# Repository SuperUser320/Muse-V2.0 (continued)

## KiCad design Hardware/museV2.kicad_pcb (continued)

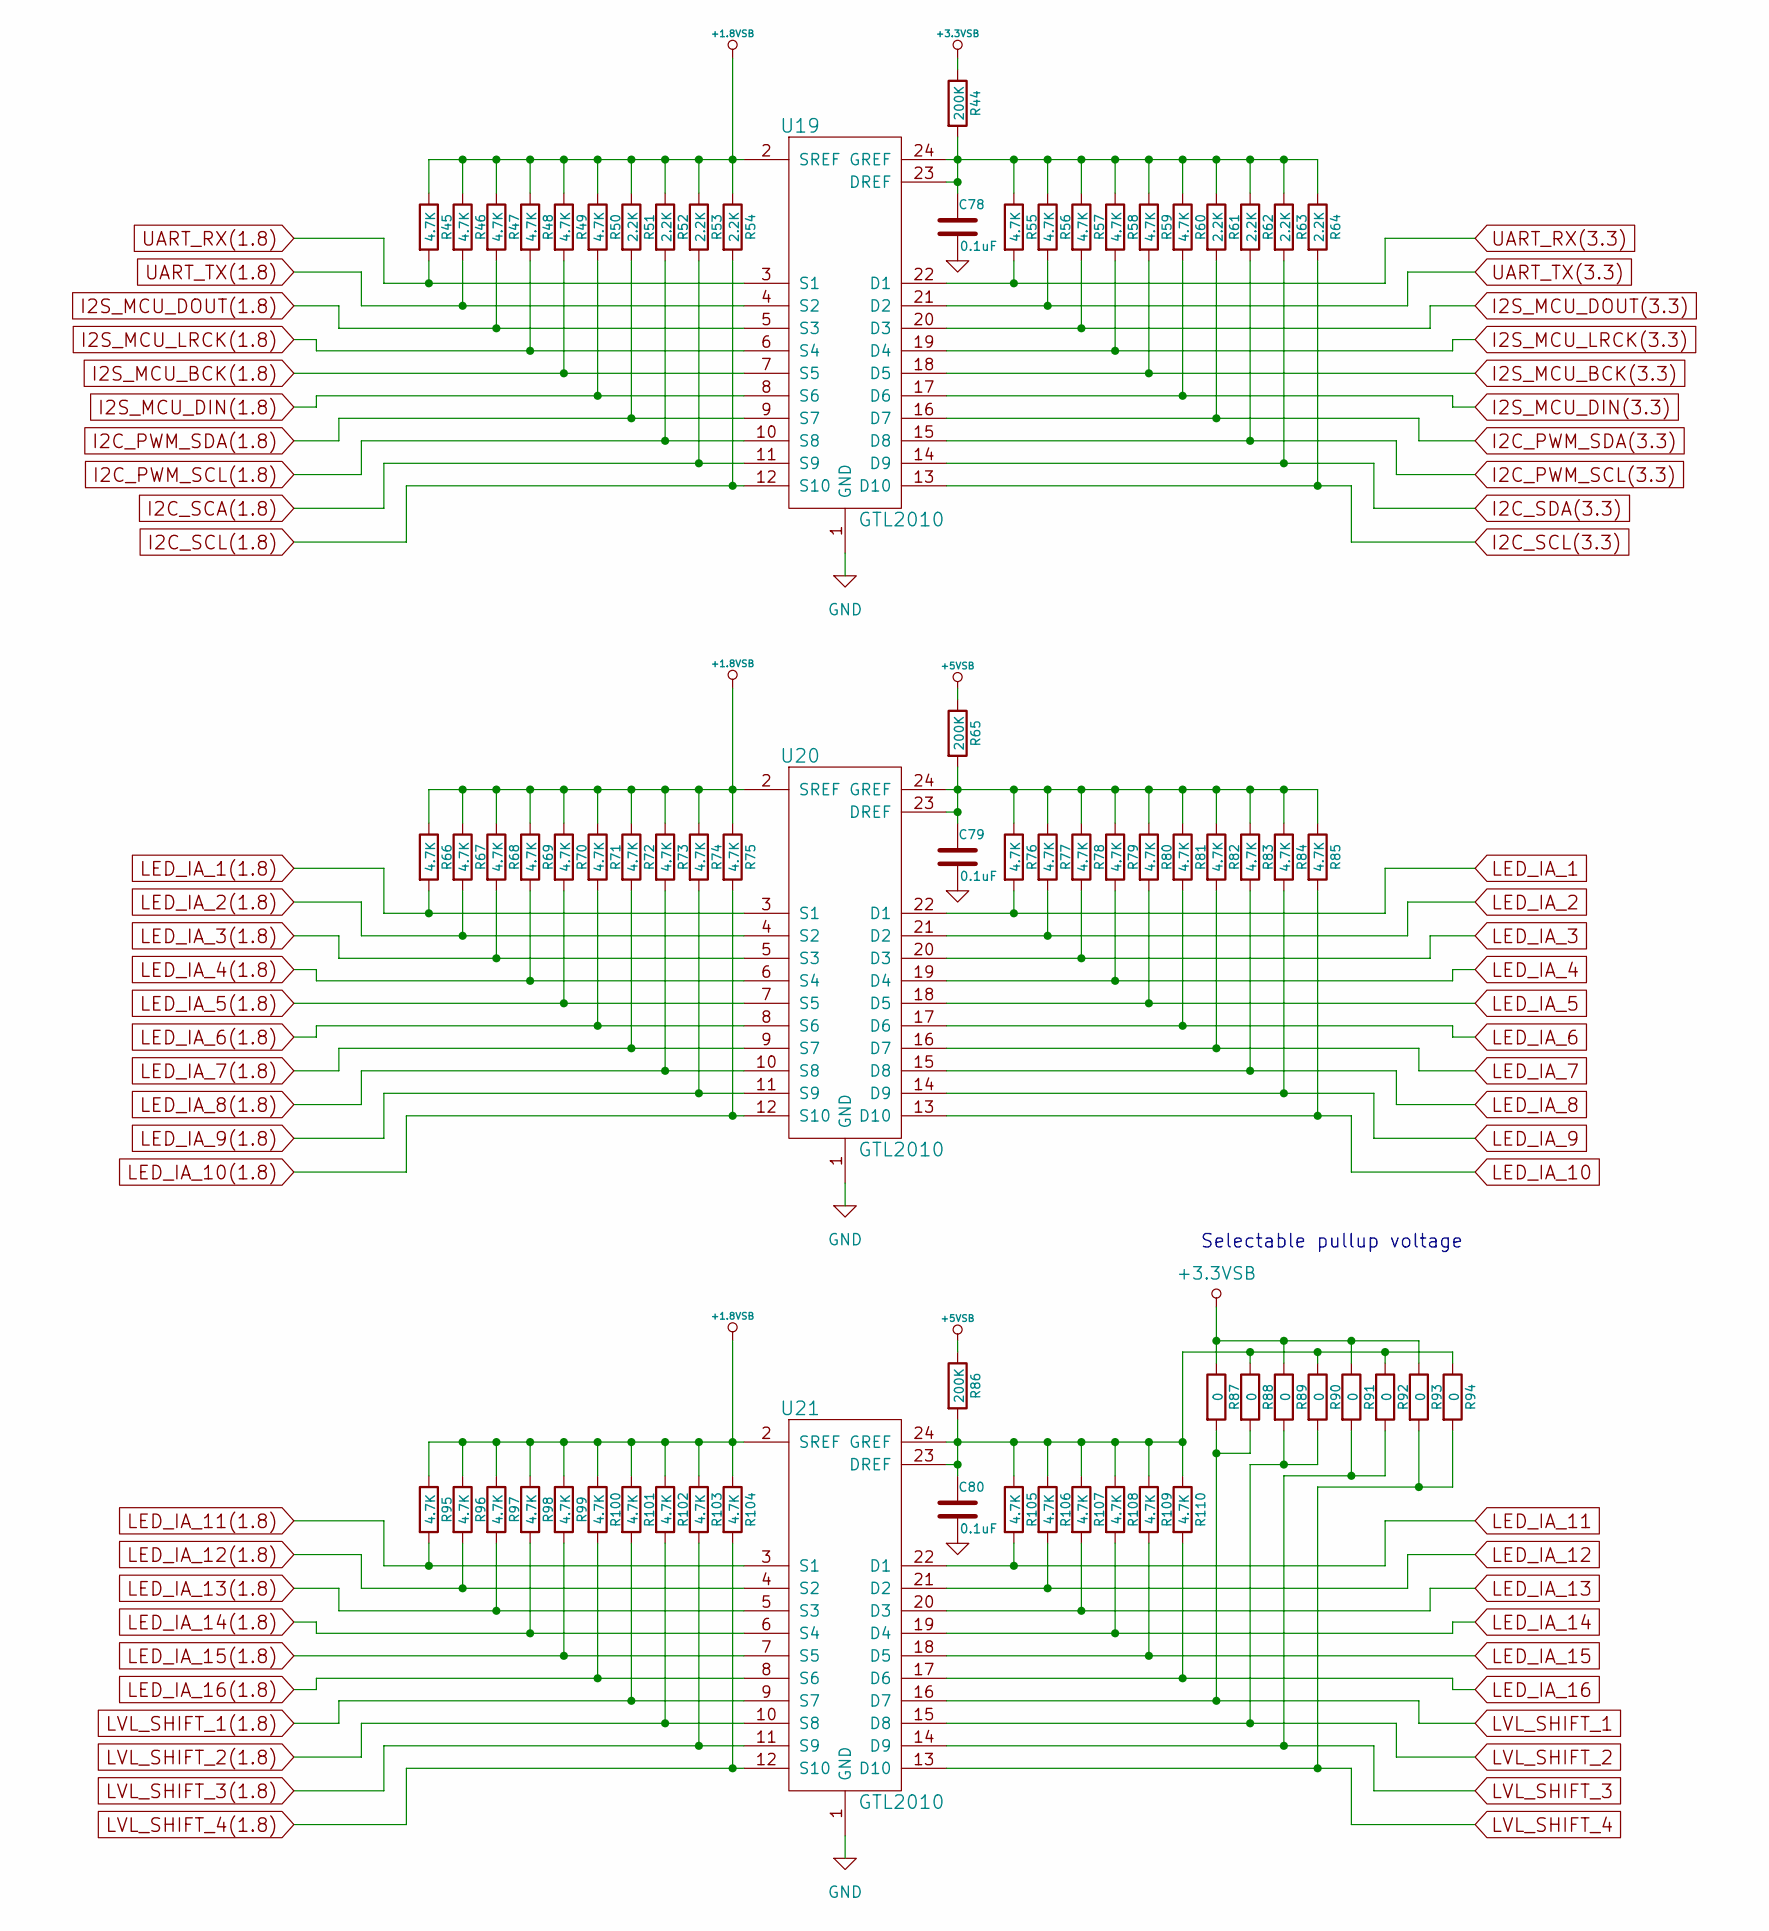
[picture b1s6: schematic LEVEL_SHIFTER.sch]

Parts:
C78, C79, C80: 0.1uF; C_0402
R44, R65, R86: 200K; R_0402
R45, R46, R47, R48, R49, R50, R55, R56, R57, R58, R59, R60, R66, R67, R68, R69, R70, R71, R72, R73, R74, R75, R76, R77, R78, R79, R80, R81, R82, R83, R84, R85, R95, R96, R97, R98, R99, R100, R101, R102, R103, R104, R105, R106, R107, R108, R109, R110: 4.7K; R_0402
R51, R52, R53, R54, R61, R62, R63, R64: 2.2K; R_0402
R87, R88, R89, R90, R91, R92, R93, R94: 0; R_0603_HandSoldering
U19, U20, U21: GTL2010; SSOP-24_5.3x8.2mm_Pitch0.65mm

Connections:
+1.8VSB: R45.1, R46.1, R47.1, R48.1, R49.1, R50.1, R51.1, R52.1, R53.1, R54.1, R66.1, R67.1, R68.1, R69.1, R70.1, R71.1, R72.1, R73.1, R74.1, R75.1, R95.1, R96.1, R97.1, R98.1, R99.1, R100.1, R101.1, R102.1, R103.1, R104.1, U19.2 (SREF), U20.2 (SREF), U21.2 (SREF); also elsewhere on the board
+3.3VSB: R44.1, R87.1, R89.1, R91.1, R93.1; also elsewhere on the board
+5VSB: R65.1, R86.1; also elsewhere on the board
GND: C78.2, C79.2, C80.2, U19.1 (GND), U20.1 (GND), U21.1 (GND); also elsewhere on the board
I2C_PWM_SCL(1.8): R52.2, U19.10 (S8); also elsewhere on the board
I2C_PWM_SCL(3.3): R62.2, U19.15 (D8); also elsewhere on the board
I2C_PWM_SDA(1.8): R51.2, U19.9 (S7); also elsewhere on the board
I2C_PWM_SDA(3.3): R61.2, U19.16 (D7); also elsewhere on the board
I2C_SCA(1.8): R53.2, U19.11 (S9); also elsewhere on the board
I2C_SCL(1.8): R54.2, U19.12 (S10); also elsewhere on the board
I2C_SCL(3.3): R64.2, U19.13 (D10); also elsewhere on the board
I2C_SDA(3.3): R63.2, U19.14 (D9); also elsewhere on the board
I2S_MCU_BCK(1.8): R49.2, U19.7 (S5); also elsewhere on the board
I2S_MCU_BCK(3.3): R59.2, U19.18 (D5); also elsewhere on the board
I2S_MCU_DIN(1.8): R50.2, U19.8 (S6); also elsewhere on the board
I2S_MCU_DIN(3.3): R60.2, U19.17 (D6); also elsewhere on the board
I2S_MCU_DOUT(1.8): R47.2, U19.5 (S3); also elsewhere on the board
I2S_MCU_DOUT(3.3): R57.2, U19.20 (D3); also elsewhere on the board
I2S_MCU_LRCK(1.8): R48.2, U19.6 (S4); also elsewhere on the board
I2S_MCU_LRCK(3.3): R58.2, U19.19 (D4); also elsewhere on the board
LED_IA_1: R76.2, U20.22 (D1); also elsewhere on the board
LED_IA_1(1.8): R66.2, U20.3 (S1); also elsewhere on the board
LED_IA_2: R77.2, U20.21 (D2); also elsewhere on the board
LED_IA_2(1.8): R67.2, U20.4 (S2); also elsewhere on the board
LED_IA_3: R78.2, U20.20 (D3); also elsewhere on the board
LED_IA_3(1.8): R68.2, U20.5 (S3); also elsewhere on the board
LED_IA_4: R79.2, U20.19 (D4); also elsewhere on the board
LED_IA_4(1.8): R69.2, U20.6 (S4); also elsewhere on the board
LED_IA_5: R80.2, U20.18 (D5); also elsewhere on the board
LED_IA_5(1.8): R70.2, U20.7 (S5); also elsewhere on the board
LED_IA_6: R81.2, U20.17 (D6); also elsewhere on the board
LED_IA_6(1.8): R71.2, U20.8 (S6); also elsewhere on the board
LED_IA_7: R82.2, U20.16 (D7); also elsewhere on the board
LED_IA_7(1.8): R72.2, U20.9 (S7); also elsewhere on the board
LED_IA_8: R83.2, U20.15 (D8); also elsewhere on the board
LED_IA_8(1.8): R73.2, U20.10 (S8); also elsewhere on the board
LED_IA_9: R84.2, U20.14 (D9); also elsewhere on the board
LED_IA_9(1.8): R74.2, U20.11 (S9); also elsewhere on the board
LED_IA_10: R85.2, U20.13 (D10); also elsewhere on the board
LED_IA_10(1.8): R75.2, U20.12 (S10); also elsewhere on the board
LED_IA_11: R105.2, U21.22 (D1); also elsewhere on the board
LED_IA_11(1.8): R95.2, U21.3 (S1); also elsewhere on the board
LED_IA_12: R106.2, U21.21 (D2); also elsewhere on the board
LED_IA_12(1.8): R96.2, U21.4 (S2); also elsewhere on the board
LED_IA_13: R107.2, U21.20 (D3); also elsewhere on the board
LED_IA_13(1.8): R97.2, U21.5 (S3); also elsewhere on the board
LED_IA_14: R108.2, U21.19 (D4); also elsewhere on the board
LED_IA_14(1.8): R98.2, U21.6 (S4); also elsewhere on the board
LED_IA_15: R109.2, U21.18 (D5); also elsewhere on the board
LED_IA_15(1.8): R99.2, U21.7 (S5); also elsewhere on the board
LED_IA_16: R110.2, U21.17 (D6); also elsewhere on the board
LED_IA_16(1.8): R100.2, U21.8 (S6); also elsewhere on the board
LVL_SHIFT_1: R87.2, R88.2, U21.16 (D7); also elsewhere on the board
LVL_SHIFT_1(1.8): R101.2, U21.9 (S7); also elsewhere on the board
LVL_SHIFT_2: R89.2, R90.2, U21.15 (D8); also elsewhere on the board
LVL_SHIFT_2(1.8): R102.2, U21.10 (S8); also elsewhere on the board
LVL_SHIFT_3: R91.2, R92.2, U21.14 (D9); also elsewhere on the board
LVL_SHIFT_3(1.8): R103.2, U21.11 (S9); also elsewhere on the board
LVL_SHIFT_4: R93.2, R94.2, U21.13 (D10); also elsewhere on the board
LVL_SHIFT_4(1.8): R104.2, U21.12 (S10); also elsewhere on the board
unnamed: C78.1, R44.2, R55.1, R56.1, R57.1, R58.1, R59.1, R60.1, R61.1, R62.1, R63.1, R64.1, U19.23 (DREF), U19.24 (GREF)
unnamed: C79.1, R65.2, R76.1, R77.1, R78.1, R79.1, R80.1, R81.1, R82.1, R83.1, R84.1, R85.1, U20.23 (DREF), U20.24 (GREF)
unnamed: C80.1, R86.2, R88.1, R90.1, R92.1, R94.1, R105.1, R106.1, R107.1, R108.1, R109.1, R110.1, U21.23 (DREF), U21.24 (GREF)
UART_RX(1.8): R45.2, U19.3 (S1); also elsewhere on the board
UART_RX(3.3): R55.2, U19.22 (D1); also elsewhere on the board
UART_TX(1.8): R46.2, U19.4 (S2); also elsewhere on the board
UART_TX(3.3): R56.2, U19.21 (D2); also elsewhere on the board

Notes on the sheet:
Selectable pullup voltage

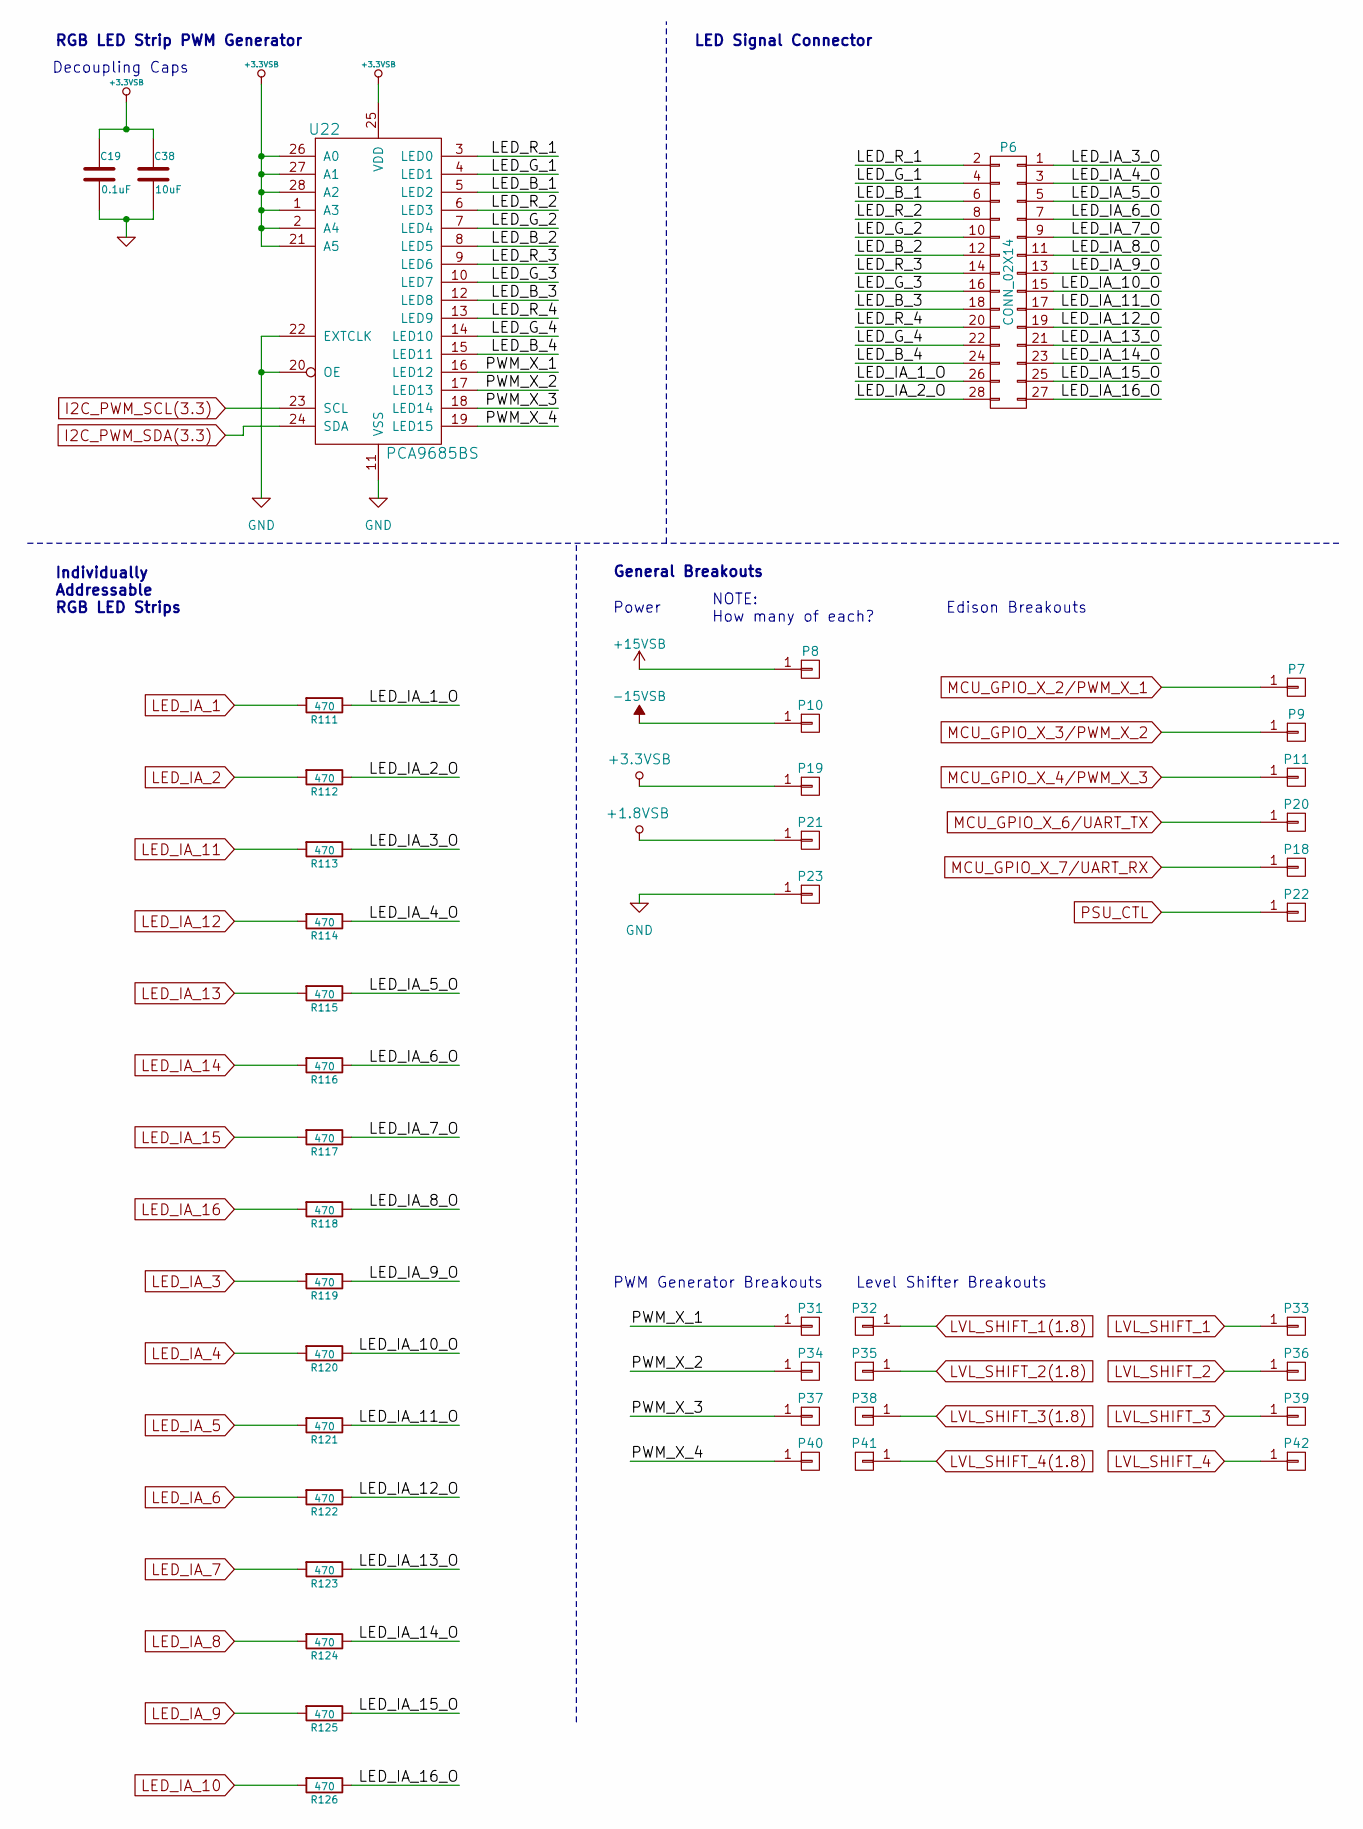
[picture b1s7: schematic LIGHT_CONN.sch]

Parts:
C19: 0.1uF; C_0402
C38: 10uF; c_elec_4x5.3
P6: CONN_02X14; Pin_Header_Straight_2x14
P7: ~1; Pin_Header_Straight_1x01
P8: +15V; Pin_Header_Straight_1x01
P9: ~2; Pin_Header_Straight_1x01
P10: -15V; Pin_Header_Straight_1x01
P11: ~3; Pin_Header_Straight_1x01
P18: RX6; Pin_Header_Straight_1x01
P19: 3.3V; Pin_Header_Straight_1x01
P20: TX5; Pin_Header_Straight_1x01
P21: 1.8V; Pin_Header_Straight_1x01
P22: PSU_CTL; Pin_Header_Straight_1x01
P23: GND; Pin_Header_Straight_1x01
P31: P1; Pin_Header_Straight_1x01
P32: L1.8_1; Pin_Header_Straight_1x01
P33: L3.3_1; Pin_Header_Straight_1x01
P34: P2; Pin_Header_Straight_1x01
P35: L1.8_2; Pin_Header_Straight_1x01
P36: L3.3_2; Pin_Header_Straight_1x01
P37: P3; Pin_Header_Straight_1x01
P38: L1.8_3; Pin_Header_Straight_1x01
P39: L3.3_3; Pin_Header_Straight_1x01
P40: P4; Pin_Header_Straight_1x01
P41: L1.8_4; Pin_Header_Straight_1x01
P42: L3.3_4; Pin_Header_Straight_1x01
R111, R112, R113, R114, R115, R116, R117, R118, R119, R120, R121, R122, R123, R124, R125, R126: 470; R_0402
U22: PCA9685BS; QFN-28-1EP_6x6mm_Pitch0.65mm_THERMAL

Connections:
+1.8VSB: P21.1; also elsewhere on the board
+3.3VSB: C19.1, C38.1, P19.1, U22.1 (A3), U22.2 (A4), U22.21 (A5), U22.25 (VDD), U22.26 (A0), U22.27 (A1), U22.28 (A2); also elsewhere on the board
+15V: P8.1; also elsewhere on the board
-15V: P10.1; also elsewhere on the board
/LIGHT_CONN/LED_B_1: P6.6, U22.5 (LED2)
/LIGHT_CONN/LED_B_2: P6.12, U22.8 (LED5)
/LIGHT_CONN/LED_B_3: P6.18, U22.12 (LED8)
/LIGHT_CONN/LED_B_4: P6.24, U22.15 (LED11)
/LIGHT_CONN/LED_G_1: P6.4, U22.4 (LED1)
/LIGHT_CONN/LED_G_2: P6.10, U22.7 (LED4)
/LIGHT_CONN/LED_G_3: P6.16, U22.10 (LED7)
/LIGHT_CONN/LED_G_4: P6.22, U22.14 (LED10)
/LIGHT_CONN/LED_IA_1_O: P6.26, R111.1
/LIGHT_CONN/LED_IA_2_O: P6.28, R112.1
/LIGHT_CONN/LED_IA_3_O: P6.1, R113.1
/LIGHT_CONN/LED_IA_4_O: P6.3, R114.1
/LIGHT_CONN/LED_IA_5_O: P6.5, R115.1
/LIGHT_CONN/LED_IA_6_O: P6.7, R116.1
/LIGHT_CONN/LED_IA_7_O: P6.9, R117.1
/LIGHT_CONN/LED_IA_8_O: P6.11, R118.1
/LIGHT_CONN/LED_IA_9_O: P6.13, R119.1
/LIGHT_CONN/LED_IA_10_O: P6.15, R120.1
/LIGHT_CONN/LED_IA_11_O: P6.17, R121.1
/LIGHT_CONN/LED_IA_12_O: P6.19, R122.1
/LIGHT_CONN/LED_IA_13_O: P6.21, R123.1
/LIGHT_CONN/LED_IA_14_O: P6.23, R124.1
/LIGHT_CONN/LED_IA_15_O: P6.25, R125.1
/LIGHT_CONN/LED_IA_16_O: P6.27, R126.1
/LIGHT_CONN/LED_R_1: P6.2, U22.3 (LED0)
/LIGHT_CONN/LED_R_2: P6.8, U22.6 (LED3)
/LIGHT_CONN/LED_R_3: P6.14, U22.9 (LED6)
/LIGHT_CONN/LED_R_4: P6.20, U22.13 (LED9)
/LIGHT_CONN/PWM_X_1: P31.1, U22.16 (LED12)
/LIGHT_CONN/PWM_X_2: P34.1, U22.17 (LED13)
/LIGHT_CONN/PWM_X_3: P37.1, U22.18 (LED14)
/LIGHT_CONN/PWM_X_4: P40.1, U22.19 (LED15)
GND: C19.2, C38.2, P23.1, U22.11 (VSS), U22.20 (OE), U22.22 (EXTCLK); also elsewhere on the board
I2C_PWM_SCL(3.3): U22.23 (SCL); also elsewhere on the board
I2C_PWM_SDA(3.3): U22.24 (SDA); also elsewhere on the board
LED_IA_1: R111.2; also elsewhere on the board
LED_IA_2: R112.2; also elsewhere on the board
LED_IA_3: R119.2; also elsewhere on the board
LED_IA_4: R120.2; also elsewhere on the board
LED_IA_5: R121.2; also elsewhere on the board
LED_IA_6: R122.2; also elsewhere on the board
LED_IA_7: R123.2; also elsewhere on the board
LED_IA_8: R124.2; also elsewhere on the board
LED_IA_9: R125.2; also elsewhere on the board
LED_IA_10: R126.2; also elsewhere on the board
LED_IA_11: R113.2; also elsewhere on the board
LED_IA_12: R114.2; also elsewhere on the board
LED_IA_13: R115.2; also elsewhere on the board
LED_IA_14: R116.2; also elsewhere on the board
LED_IA_15: R117.2; also elsewhere on the board
LED_IA_16: R118.2; also elsewhere on the board
LVL_SHIFT_1: P33.1; also elsewhere on the board
LVL_SHIFT_1(1.8): P32.1; also elsewhere on the board
LVL_SHIFT_2: P36.1; also elsewhere on the board
LVL_SHIFT_2(1.8): P35.1; also elsewhere on the board
LVL_SHIFT_3: P39.1; also elsewhere on the board
LVL_SHIFT_3(1.8): P38.1; also elsewhere on the board
LVL_SHIFT_4: P42.1; also elsewhere on the board
LVL_SHIFT_4(1.8): P41.1; also elsewhere on the board
MCU_GPIO_X_2/PWM_X_1: P7.1; also elsewhere on the board
MCU_GPIO_X_3/PWM_X_2: P9.1; also elsewhere on the board
MCU_GPIO_X_4/PWM_X_3: P11.1; also elsewhere on the board
MCU_GPIO_X_6/UART_TX: P20.1; also elsewhere on the board
MCU_GPIO_X_7/UART_RX: P18.1; also elsewhere on the board
PSU_CTL: P22.1; also elsewhere on the board

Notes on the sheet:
Individually Addressable RGB LED Strips
RGB LED Strip PWM Generator
LED Signal Connector
General Breakouts
NOTE: How many of each?
Power
Edison Breakouts
Level Shifter Breakouts
PWM Generator Breakouts
Decoupling Caps

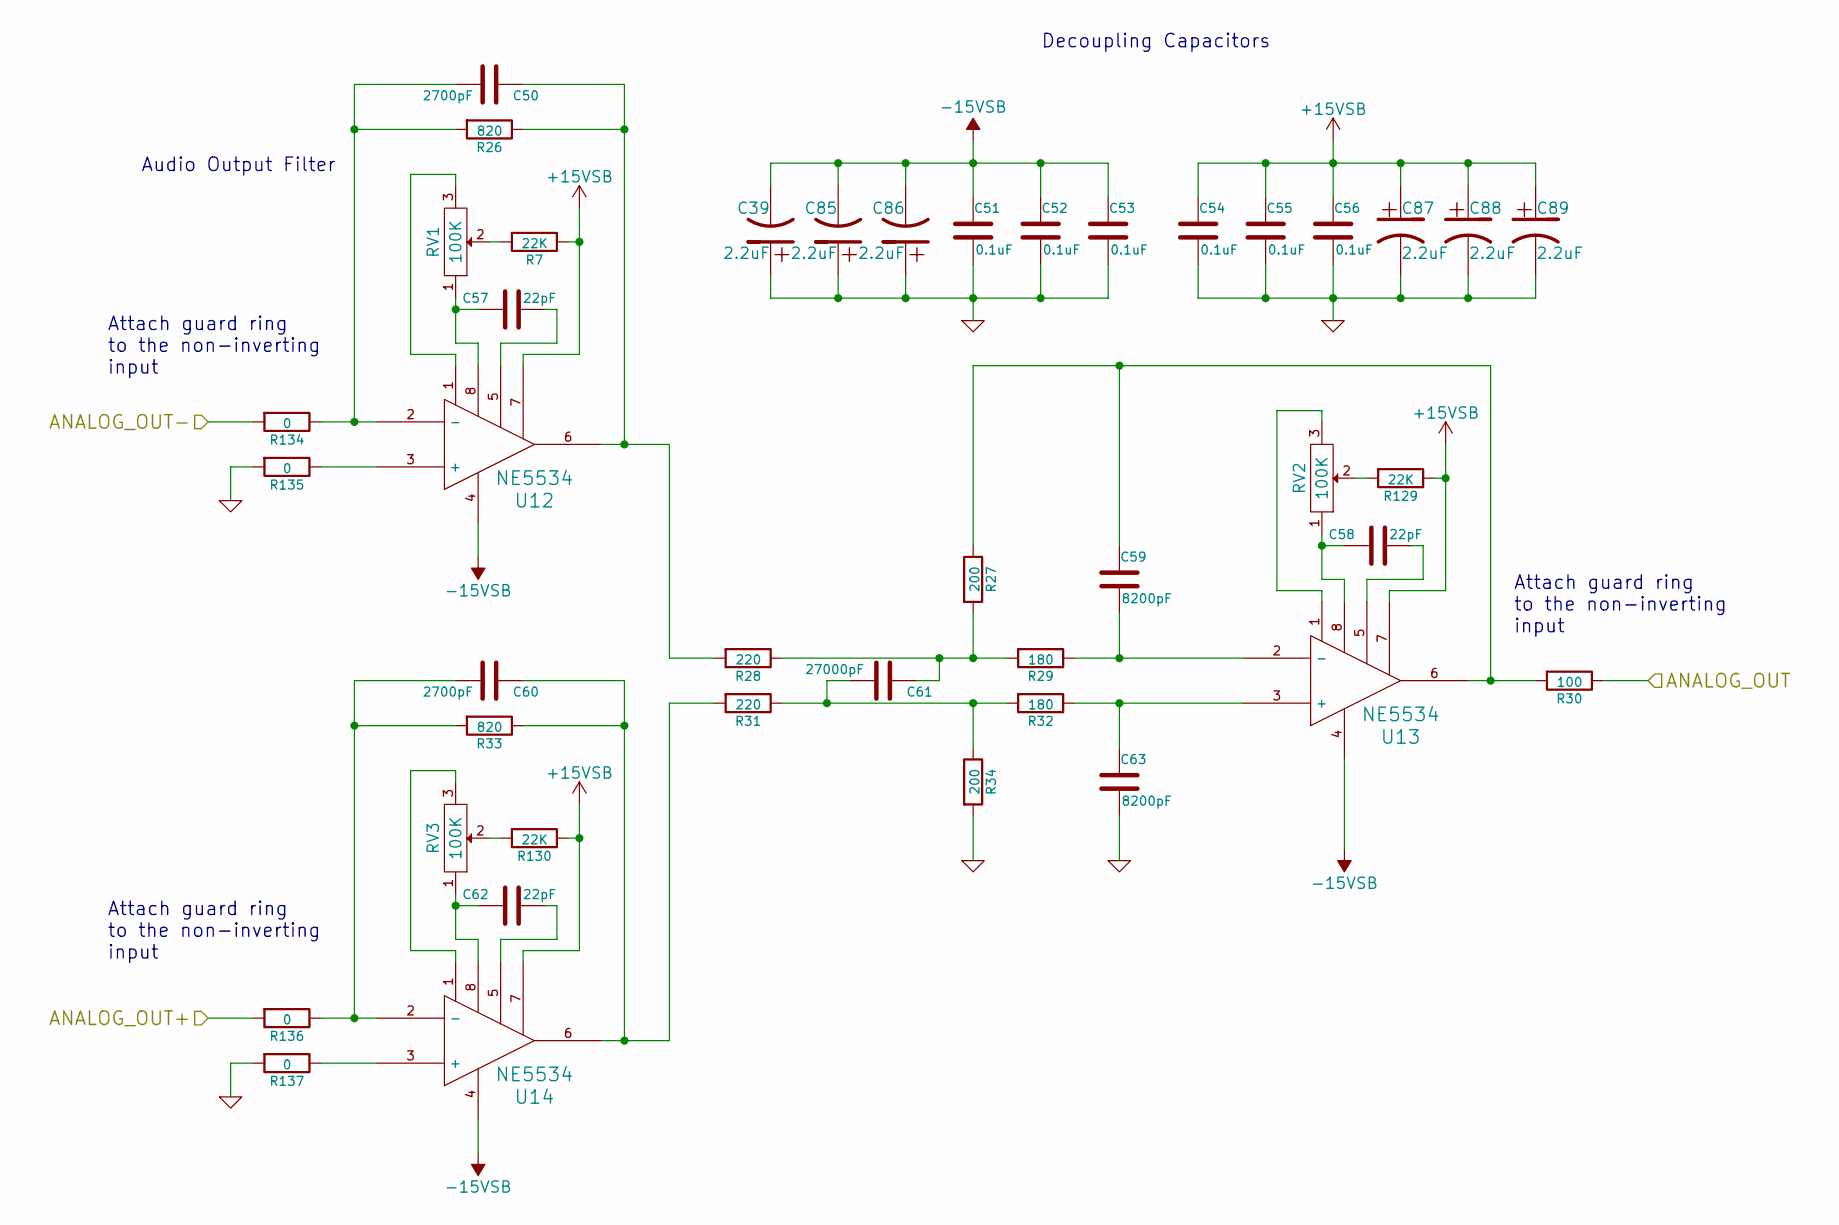
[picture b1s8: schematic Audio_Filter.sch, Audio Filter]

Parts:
C39, C85, C86, C87, C88, C89: 2.2uF; c_elec_4x5.3
C50, C60: 2700pF; C_0402
C51, C52, C53, C54, C55, C56: 0.1uF; C_0402
C57, C58, C62: 22pF; C_0402
C59, C63: 8200pF; C_0402
C61: 27000pF; C_0402
R7, R132, R133: 22K; R_0402
R26, R33: 820; R_0402
R27, R34: 200; R_0402
R28, R31: 220; R_0402
R29, R32: 180; R_0402
R30: 100; R_0402
R134, R135, R136, R137: 0; R_0402
RV1, RV3, RV5: 100K; TC33X-1
U12, U13, U14: NE5534; SOIC-8_3.9x4.9mm_Pitch1.27mm

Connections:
+15V: C54.1, C55.1, C56.1, C87.1, C88.1, C89.1, R7.1, R132.1, R133.1, U12.7, U13.7, U14.7; also elsewhere on the board
-15V: C39.2, C51.1, C52.1, C53.1, C85.2, C86.2, U12.4, U13.4, U14.4; also elsewhere on the board
/DAC/sheet57F8A4E6/ANALOG_OUT+: R136.2; also elsewhere on the board
/DAC/sheet57F8A4E6/ANALOG_OUT-: R134.2; also elsewhere on the board
ANALOG_OUT_L: R30.1; also elsewhere on the board
GND: C39.1, C51.2, C52.2, C53.2, C54.2, C55.2, C56.2, C63.2, C85.1, C86.1, C87.2, C88.2, C89.2, R34.2, R135.2, R137.2; also elsewhere on the board
unnamed: C50.1, R26.1, R28.2, U12.6
unnamed: C50.2, R26.2, R134.1, U12.2 (-)
unnamed: C57.1, RV1.1, U12.8
unnamed: C57.2, U12.5
unnamed: C58.2, U13.5
unnamed: C59.1, R27.1, R30.2, U13.6
unnamed: C59.2, R29.1, U13.2 (-)
unnamed: C60.1, R31.2, R33.1, U14.6
unnamed: C60.2, R33.2, R136.1, U14.2 (-)
unnamed: C61.1, R27.2, R28.1, R29.2
unnamed: C61.2, R31.1, R32.2, R34.1
unnamed: C62.1, RV3.1, U14.8
unnamed: C62.2, U14.5
unnamed: C63.1, R32.1, U13.3 (+)
unnamed: R7.2, RV1.2
unnamed: R132.2, RV5.2
unnamed: R135.1, U12.3 (+)
unnamed: R137.1, U14.3 (+)
unnamed: RV1.3, U12.1
unnamed: RV3.3, U14.1

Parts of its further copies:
C64, C74: 2700pF; C_0402
C65, C66, C67, C68, C69, C70: 0.1uF; C_0402
C71, C72, C76: 22pF; C_0402
C73, C77: 8200pF; C_0402
C75: 27000pF; C_0402
C81, C82, C83, C84, C90, C91: 2.2uF; c_elec_4x5.3
R35, R42: 820; R_0402
R36, R43: 200; R_0402
R37, R40: 220; R_0402
R38, R41: 180; R_0402
R39: 100; R_0402
R129, R130, R131: 22K; R_0402
R138, R139, R140, R141: 0; R_0402
RV2, RV4, RV6: 100K; TC33X-1
U15, U16, U17: NE5534; SOIC-8_3.9x4.9mm_Pitch1.27mm

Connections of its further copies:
+15V: C68.1, C69.1, C70.1, C83.1, C84.1, C91.1, R129.1, R130.1, R131.1, U15.7, U16.7, U17.7; also elsewhere on the board
-15V: C65.1, C66.1, C67.1, C81.2, C82.2, C90.2, U15.4, U16.4, U17.4; also elsewhere on the board
/DAC/sheet57F8A4E7/ANALOG_OUT+: R140.2; also elsewhere on the board
/DAC/sheet57F8A4E7/ANALOG_OUT-: R138.2; also elsewhere on the board
ANALOG_OUT_R: R39.1; also elsewhere on the board
GND: C65.2, C66.2, C67.2, C68.2, C69.2, C70.2, C77.2, C81.1, C82.1, C83.2, C84.2, C90.1, C91.2, R43.2, R139.2, R141.2; also elsewhere on the board
unnamed: C64.1, R35.1, R37.2, U15.6
unnamed: C64.2, R35.2, R138.1, U15.2 (-)
unnamed: C71.1, RV4.1, U15.8
unnamed: C71.2, U15.5
unnamed: C72.2, U16.5
unnamed: C73.1, R36.1, R39.2, U16.6
unnamed: C73.2, R38.1, U16.2 (-)
unnamed: C74.1, R40.2, R42.1, U17.6
unnamed: C74.2, R42.2, R140.1, U17.2 (-)
unnamed: C75.1, R36.2, R37.1, R38.2
unnamed: C75.2, R40.1, R41.2, R43.1
unnamed: C76.1, RV6.1, U17.8
unnamed: C76.2, U17.5
unnamed: C77.1, R41.1, U16.3 (+)
unnamed: R129.2, RV2.2
unnamed: R131.2, RV4.2
unnamed: R139.1, U15.3 (+)
unnamed: R141.1, U17.3 (+)
unnamed: RV4.3, U15.1
unnamed: RV6.3, U17.1

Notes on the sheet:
Audio Output Filter
Decoupling Capacitors
Attach guard ring to the non-inverting input

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
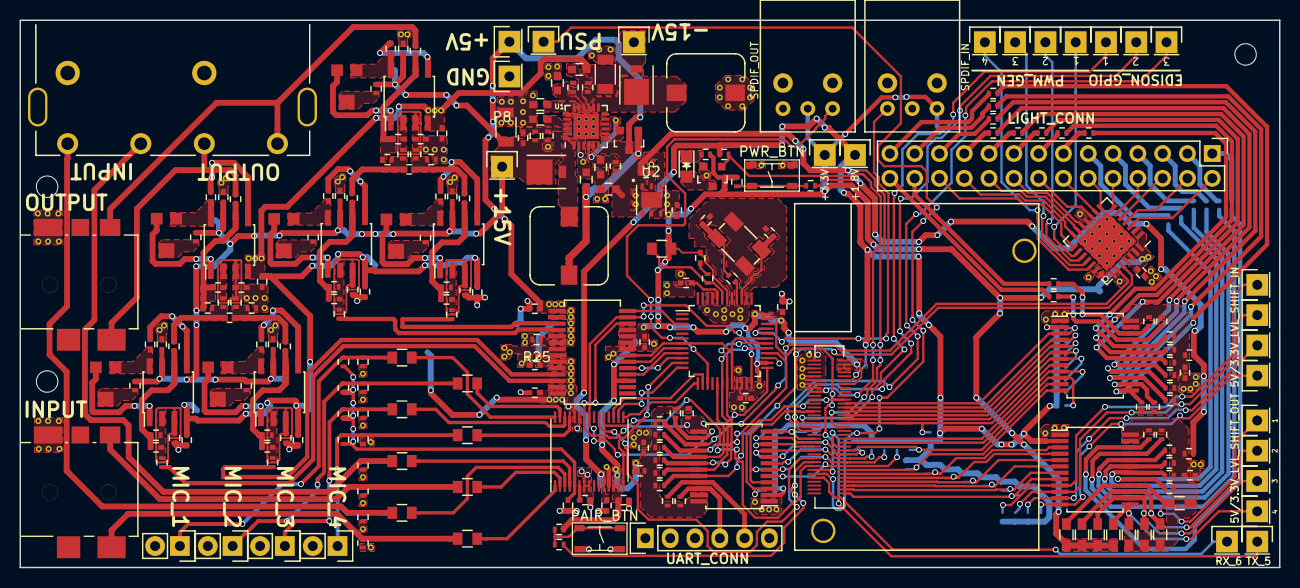
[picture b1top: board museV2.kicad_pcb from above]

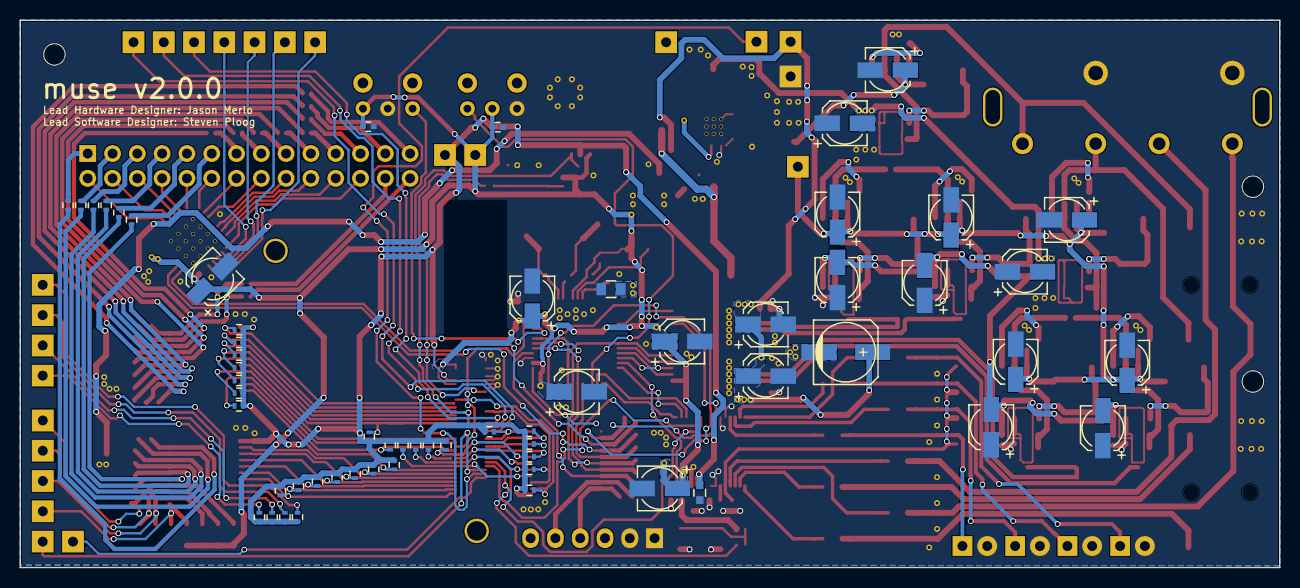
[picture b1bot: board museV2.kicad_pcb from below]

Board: 2 copper layers, 129.0 x 56.1 mm, 299 parts (60 on the bottom side), 216 nets.

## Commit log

2016-09-06 Initial Commit to Open Source
2016-09-11 Added Lighting Connectors
2016-09-13 Added missing i2s pins to Edison
2016-09-13 Added Microphones and Mic Bias
2016-09-13 Added ADC interrupt output pins to Edison
2016-09-13 Corrected DFE GPIO Data Port Connections
2016-09-13 Added LED Strip Current Limiting Resistor
    Added PSU surge protection caps
2016-09-13 Added Aux ATX Power connector, reorganized layout
2016-09-13 Annotated
2016-09-13 Added Pull-down & Gate Resistors to MOSFETs
2016-09-14 Updated U8 reference location, Fixed Windows complaints
2016-09-14 Changed DAC to SB Power
2016-09-14 Fixed SPDIF labels,
2016-09-14 Added split rail PS for DAC SB power
2016-09-14 Updated op-amp power supply to +/-15VSB
2016-09-15 Disconnected Zeros on DAC
    moved ADC pins on DFE as recommended by datasheet
2016-09-20 Added level shifter, moved LEDs to their own sheet
2016-09-20 Added PWM generator, More Shift Regs
    Moved GPIO pins on MUSE
2016-09-22 Syncing changes from 9/20 meeting
2016-09-25 Currently adding level shifters
2016-09-29 Finished level shifter sheet
2016-09-30 In progress changing to global labels
2016-10-06 Changing to global labels/pages in progress
2016-10-08 Finished converting to global labels
2016-10-09 Updated I2C pullup resistors and labels
2016-10-13 Made design review fixes, added breakouts
2016-10-14 Annotated schematic
2016-11-04 Pushing most updated version
2016-11-15 Annotation/Part Selection BOM Update
2016-12-20 Added bluetooth pair button
2016-12-20 Add footprints to capacitor netlist
2016-12-20 Added MacroFab house parts kicad library
2016-12-20 Fixing schematic issues
2016-12-20 Fixed schematic errors, added muse-v2-lib
2016-12-20 Add footprint for SPDIF out
2016-12-20 Added DO-216-AA to lib
2016-12-20 Add courtyard to SPDIF connector
2016-12-21 Added 7.3mm Inductor footprint to lib
2016-12-21 Added WSON6 footprint
2016-12-21 Added RCA connector to footprint lib
2016-12-21 Added 3.5mm audio jack to footprint lib
2016-12-21 Added Microphone to footprint lib
2016-12-21 Added TSSOP30 to footprint lib
2016-12-21 Added proper audio connectors to schematic
2016-12-21 Updated Edison pins for 3.5mm connections
2016-12-21 Added crystal footprint to lib
2016-12-21 Adjust placement of pin 3 to match datasheet
2016-12-22 Updated libraries and place components into board layout
2016-12-22 Updated small schematic changes
2016-12-22 Updated QFN footprints with thermal evacuation vias
2016-12-22 Routing split rail DC/DC converter
2016-12-26 PCB Layout progress - placing PCM9211 components
2016-12-26 Placing ADC connections
2016-12-26 routing digital signal wires
2016-12-30 Completed placement of level shifters
2016-12-31 Digital Half completed placement
2017-01-01 Beginning analog chip placement
2017-01-04 Op-Amp placement and wiring
2017-01-04 Continuing placement of op-amps
2017-01-04 (Digital) board fixes
2017-01-04 Nearing end of op-amp placement
2017-01-05 All tracks and planes filled. Fixing fill intersections and missing power/gnd connections
2017-01-05 Rev 2.0.0 finished. Ready for design review.
2017-01-05 Updated text
2017-01-07 Initial commit of web server and web app work. Use npm install to install deps.
    Includes dummy directories for 4 visualizers.
    .gitignore for node_modules folder
    Some very basic functionality in files that will need to be renamed as time goes on.
2017-01-07 Get ids of all list elements in order and log them
2017-01-07 Inline styling for some nice-ish alignment of everything
2017-01-07 Mounting holes added
2017-01-07 Send display/not display lists to server in post. Log at server.
    Also switch all single quotes to double quotes
2017-01-08 Add gitignore for hidden and shown visualizer data files
2017-01-08 Save and load visualizers in order on settings page
2017-01-08 Rename home.pug to settings.pug.
2017-01-08 Create control.pug file. Correct references to home.pug in visualizer.js
    Set titles of webpages.
2017-01-08 Move frontend files to frontend folder
2017-01-08 Add new directories to visualizer.js
2017-01-08 Remove dummy line in settings. Add frontend folder to files that are served
2017-01-08 Added control page functionality.
    Control page now displays buttons for each visualizer in the order they are set in settings.
2017-01-08 Some CSS updates
2017-01-08 Add refresh visualizer list handling and error checking
